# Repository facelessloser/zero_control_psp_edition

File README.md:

# zero_control_psp_edition
zero_control_psp_edition

tinkerboy arduino code from here https://www.tinkerboy.xyz/arduino-usb-gamepad

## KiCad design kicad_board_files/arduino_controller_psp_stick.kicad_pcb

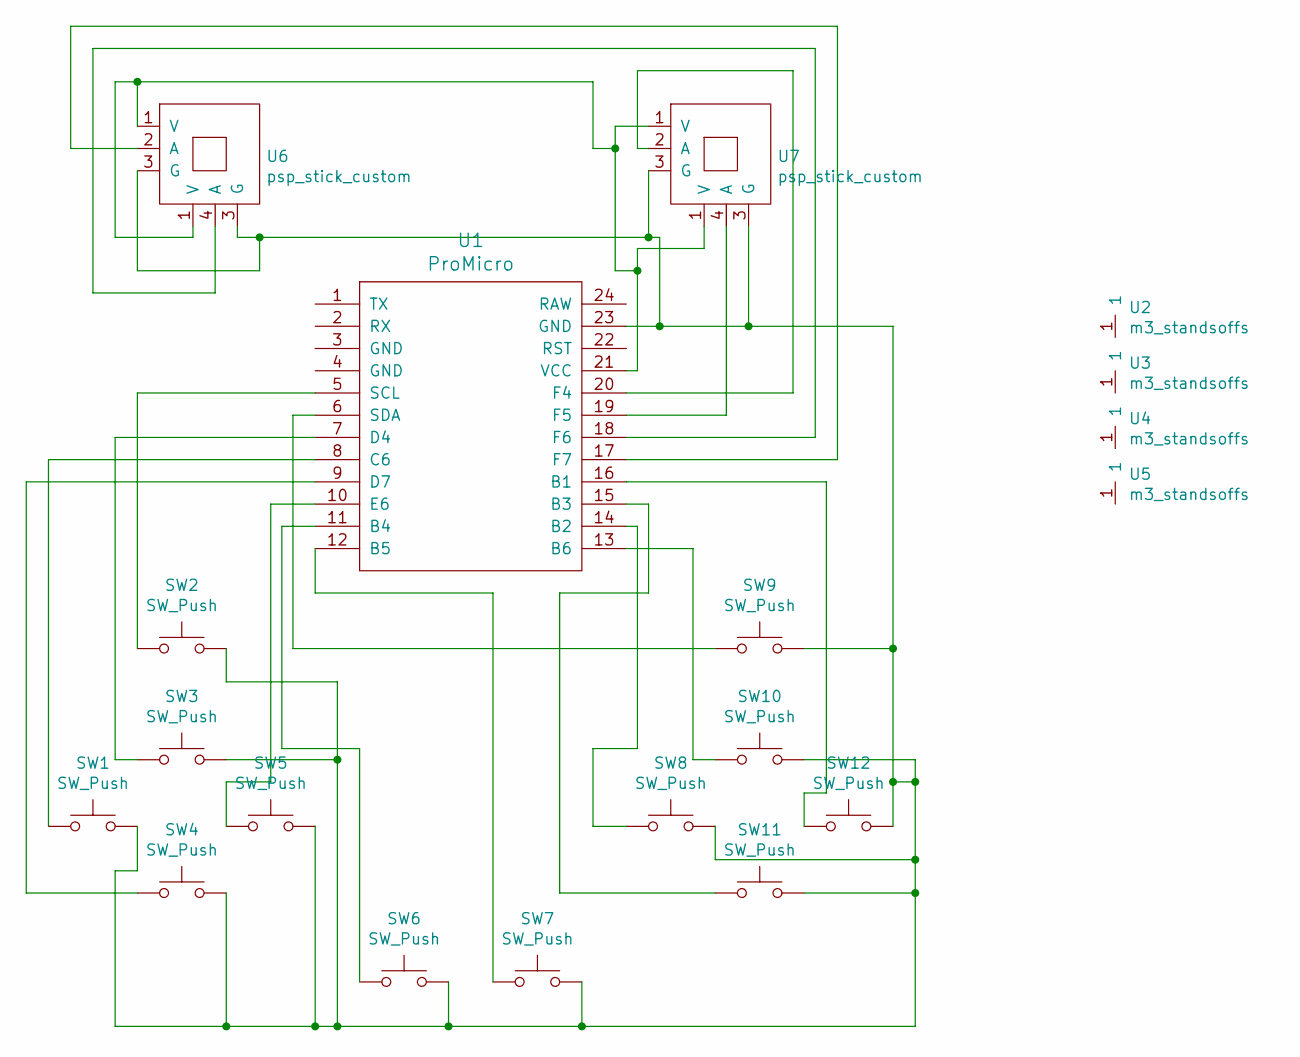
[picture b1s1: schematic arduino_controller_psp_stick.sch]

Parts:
SW1, SW2, SW3, SW4, SW5, SW6, SW7, SW8, SW9, SW10: SW_Push; smd_soft_custom
SW11, SW12: SW_Push; right_angle_2_pin
U1: ProMicro
U2, U3, U4, U5: m3_standsoffs; m3_hole_custom
U6, U7: psp_stick_custom; psp_stick_6pin_custom

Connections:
unnamed: SW1.1, U1.8 (C6)
unnamed: SW1.2, SW2.2, SW3.2, SW4.2, SW5.2, SW6.2, SW7.2, SW8.2, SW9.2, SW10.2, SW11.2, SW12.2, U1.23 (GND), U6.3 (G), U7.3 (G)
unnamed: SW2.1, U1.5 (SCL)
unnamed: SW3.1, U1.7 (D4)
unnamed: SW4.1, U1.9 (D7)
unnamed: SW5.1, U1.10 (E6)
unnamed: SW6.1, U1.11 (B4)
unnamed: SW7.1, U1.12 (B5)
unnamed: SW8.1, U1.14 (B2)
unnamed: SW9.1, U1.6 (SDA)
unnamed: SW10.1, U1.13 (B6)
unnamed: SW11.1, U1.15 (B3)
unnamed: SW12.1, U1.16 (B1)
unnamed: U1.17 (F7), U6.2 (A)
unnamed: U1.18 (F6), U6.4 (A)
unnamed: U1.19 (F5), U7.4 (A)
unnamed: U1.20 (F4), U7.2 (A)
unnamed: U1.21 (VCC), U6.1 (V), U7.1 (V)

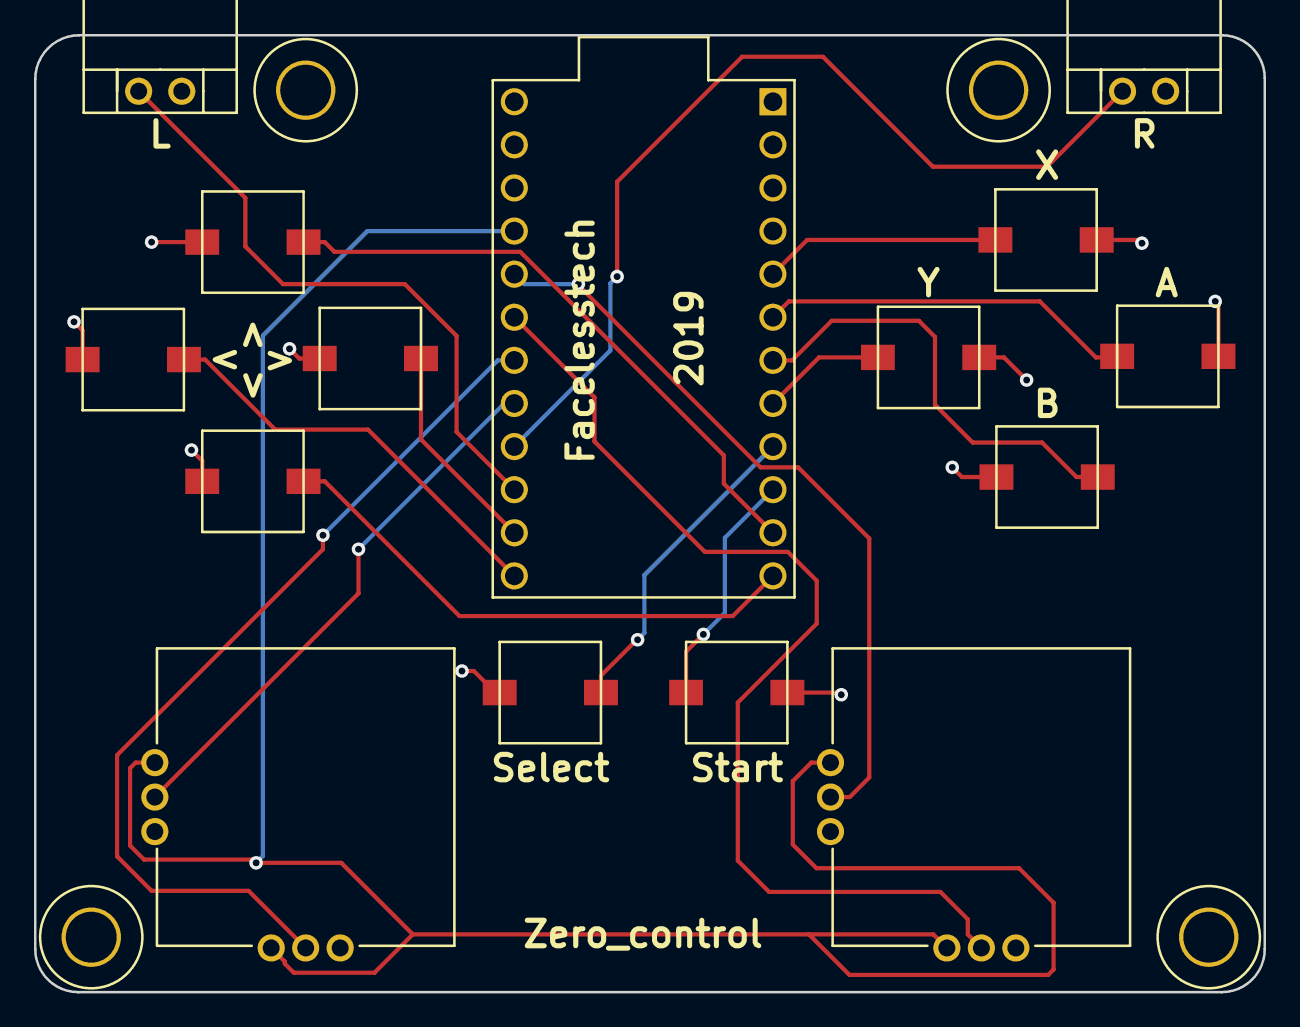
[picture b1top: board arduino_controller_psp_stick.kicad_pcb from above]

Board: 2 copper layers, 72.5 x 56.4 mm, 19 parts (1 on the bottom side), 18 nets.

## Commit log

2019-06-07 board files
2019-06-07 added link
2019-06-08 first upload of code
2019-06-08 added link to tinkerboy blog post
2019-06-08 board files to make the right angle buttons
2019-07-07 dual sticks
